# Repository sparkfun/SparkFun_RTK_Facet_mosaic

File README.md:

SparkPNT RTK Facet mosaic
========================================

[*SparkPNT RTK Facet mosaic (GPS-29688)*](https://www.sparkfun.com/sparkpnt-rtk-facet-mosaic.html)

Designed and manufactured in Boulder, Colorado, USA, and utilizing the multi-band mosaic-X5 from Septentrio, the [SparkPNT RTK Facet mosaic](https://www.sparkfun.com/sparkpnt-rtk-facet-mosaic.html) is *the* top of the line receiver for high precision geolocation and surveying needs. For basic users, it's incredibly easy to get up and running; for advanced users, the RTK Facet mosaic is a flexible and powerful tool. With just the press of a button, the RTK Facet mosaic is the fastest way to take centimeter-grade measurements. With a [subscription to the PointPerfect Flex NTRIP/RTCM service](https://www.sparkfun.com/rtk_facet_mosaic_registration) or any other corrections service, 10mm Real Time Kinematic fixes are less than a minute away. By connecting your phone to the RTK Facet mosaic over Bluetooth®, your phone or tablet can receive the NMEA output and work with most GIS software programs. This is exactly how $10,000 surveying devices have been operating for the past decade - we just made it faster, more precise, and a lot more economical.

The RTK Facet mosaic works with common GIS software for Android and iOS including SW Maps [Android](https://sparkfun.github.io/SparkFun_RTK_Firmware/gis_software/#sw-maps) / [iOS](https://apps.apple.com/us/app/sw-maps/id6444248083), [Field Genius](https://www.microsurvey.com/products/fieldgenius-for-android/), [SurvPC](https://www.carlsonsw.com/product/carlson-survce), [Survey Master](https://docs.sparkfun.com/SparkFun_RTK_Firmware/gis_software/#survey-master), [Vespucci](https://play.google.com/store/apps/details?id=de.blau.android&hl=en_US&gl=US), [QGIS](https://qgis.org/), [QField](https://docs.qfield.org/get-started/), and any GIS software that supports NMEA over Bluetooth.

Under the hood of the SparkPNT RTK Facet mosaic is an ESP32-WROVER-E connected to a mosaic-X5 GNSS multi-band receiver, and a variety of peripheral hardware (LiPo fuel gauge, microSD, etc). Additionally, housed under the dome of the RTK Facet mosaic is a surveyor grade L1/L2/L5 antenna. This antenna is a unique combination of elements designed to receive the GNSS signals (L1/L2/L5). The RTK Facet mosaic is programmed in Arduino and can be tailored by you to fit whatever your needs may be.

This device can be used in five modes:

- GNSS Positioning (~30cm accuracy) - also known as **Rover**
- GNSS Positioning with RTK (1.4cm accuracy) - also known as **Rover with RTK Fix**
- GNSS **Base Station**
- GNSS **Base Station NTRIP Server**

At *Power On* the device will enter **Rover** or **Base** mode; whichever state the device was in at the last power down. When the POWER/SETUP button is pressed momentarily, a menu is presented to change the RTK Facet mosaic from *Rover to Base mode* or vice-versa. The display will indicate the change with a small car *(Rover)* or flag *(Base)* icon.

In **Rover mode** the RTK Facet mosaic will receive `L1`, `L2`, and `L5` GNSS signals from the four constellations (GPS, GLONASS, Galileo, and BeiDou) and calculate the position based on these signals. Similar to a standard grade GPS receiver, the RTK Facet mosaic will output industry standard NMEA sentences at 4Hz and broadcast them over any paired Bluetooth® device. The end user will need to parse the NMEA sentences using commonly available mobile apps, GIS products, or embedded devices (there are many open source libraries). Unlike standard grade GPS receivers that have **2500mm** accuracy, the accuracy in this mode is approximately **300mm** horizontal positional accuracy. When RTCM correction data is sent over Bluetooth® or into the radio port, the device will automatically enter Positioning with RTK mode. In this mode RTK Facet mosaic will receive `L1`/`L2`/`L5` signals from the antenna and correction data from a base station. The receiver will quickly (within a second) obtain an RTK float, then fix. The NMEA sentences will have increased accuracy of 10mm horizontal and 10mm vertical accuracy. The RTCM correction data is most easily obtained over the Internet using a free app on your phone (see our SW Maps *([Android](http://docs.sparkfun.com/SparkFun_RTK_Everywhere_Firmware/gis_software_android/#sw-maps)/[iOS](http://docs.sparkfun.com/SparkFun_RTK_Everywhere_Firmware/gis_software_ios/#sw-maps))* or [Lefebure NTRIP](http://docs.sparkfun.com/SparkFun_RTK_Everywhere_Firmware/gis_software_android/#lefebure) instructions) and sent over Bluetooth® to the RTK Facet mosaic. However, RTCM correction data can also be received over an external cellular or radio link from a 2nd RTK Torch, Postcard, Facet mosaic, Surveyor, Express, etc. that is setup as a base station.

In **Base mode** the device will enter Base Station mode. This is used when the device is mounted to a fixed position (like a tripod or roof). The RTK Facet mosaic will initiate a survey. After 60 to 120 seconds the survey will complete and the RTK Facet mosaic will begin transmitting RTCM correction data out the radio port. A base is often used in conjunction with a second RTK Facet mosaic (or RTK Surveyor, Express, Express Plus, etc) unit set to *Rover* to obtain the 10mm accuracy. Said differently, the Base sits still and sends correction data to the Rover, so that the Rover can output really accurate position data for its location.

In addition to supplying position data, the RTK Facet mosaic is capable of logging NMEA, RAWX, and SFRBX for post processing making it ideal for research and advanced positioning applications.

The RTK Facet mosaic is an open source hardware product meaning you can fully obtain, see, and even modify the electrical and mechanical design files. This allows for easier maintenance and repair over time.

The SparkPNT RTK Facet mosaic kit includes everything you need: the enclosed device, thread adapter, charger, data cables, and carrying case. It does **NOT** include a [surveying pole](https://www.sparkfun.com/telescopic-surveying-pole.html) *(any additional items will need to be purchased separately)*.

> [!IMPORTANT]
> The SparkPNT RTK Facet mosaic is not designed for permanent outdoor mounting. Please use the [RTK mosaic-X5](https://www.sparkpnt.com/products/sparkpnt-sxm-e-cors) or the [RTK Reference Station](https://www.sparkfun.com/sparkfun-rtk-reference-station.html) that is located inside or protected from the elements. Or, for a DIY solution, the [ESP32](https://www.sparkfun.com/sparkfun-thing-plus-esp32-wroom-micro-b.html) attached to our [ZED-F9P breakout](https://www.sparkfun.com/sparkfun-gps-rtk-sma-breakout-zed-f9p-qwiic.html) is a great way to go. See our [How to Build a DIY GNSS Reference Station](https://learn.sparkfun.com/tutorials/how-to-build-a-diy-gnss-reference-station) tutorial for more information.

> [!NOTE]
> The [RTK Everywhere firmware](https://github.com/sparkfun/SparkFun_RTK_Everywhere_Firmware) is open-source, so users can obtain, check, and even modify the device's functionality. This allows for easier feature expansion, bug maintenance, and longer device longevity.

Documentation
--------------

- **[Hookup Guide (mkdocs)](http://docs.sparkfun.com/SparkFun_RTK_Facet_mosaic/)** - The hookup guide for the SparkPNT RTK Facet mosaic hosted by GitHub pages.<br>
   
- [User Manual - RTK Everywhere Firmware](https://docs.sparkfun.com/SparkFun_RTK_Everywhere_Firmware/) - Documentation for the [RTK Everywhere firmware](https://github.com/sparkfun/SparkFun_RTK_Everywhere_Firmware)

*Need to download or print our hookup guide?*

- [Print *(Print to PDF)* from Single-Page View](http://docs.sparkfun.com/SparkFun_RTK_Facet_mosaic/print_view)

Repository Contents
-------------------

- **[/docs](/docs/)** - Online documentation files
	- [assets](/docs/assets/) - Assets files
		- [3d_model](/docs/assets/3d_model/) - Files for the 3D models
			- [3D CAD Models](/docs/assets/3d_model/step_files.zip) (.step)
		- [board_files](/docs/assets/board_files/) - Files for the product design
			- [KiCad Design Files](/docs/assets/board_files/kicad_files.zip) (.zip)
			- [Schematics](/docs/assets/board_files/schematics.zip) (.pdf)
			<!-- - [Dimensions](/docs/assets/board_files/dimensions.pdf) (.pdf) -->
		- [component_documentation](/docs/assets/component_documentation/) - Datasheets for hardware components
		- [img/hookup_guide/](/docs/assets/img/hookup_guide/) - Images for hookup guide documentation
- **[/Enclosure](/Enclosure/)** - CAD model for an enclosure
- **[/Hardware](/Hardware/)** - Hardware design files (.brd, .sch)
	- **[/Production](/Production/)** - Production files

Product Variants
----------------

- [GPS-24903](https://www.sparkfun.com/sparkpnt-rtk-facet-mosaic-l-band.html) - v1.0, Initial Release
- [GPS-29688](https://www.sparkfun.com/sparkpnt-rtk-facet-mosaic.html) - Rename the product to remove "L-Band" from the name. This is due to u-blox's choice to discontinue the L-Band service to North America starting on December 31st, 2025.

- Facet Product Line
	- [GPS-20000](https://www.sparkfun.com/sparkfun-rtk-facet-l-band.html) - SparkFun RTK Facet L-Band
	- [GPS-19984](https://www.sparkfun.com/sparkfun-rtk-facet.html) - SparkFun RTK Facet
	- [GPS-19029](https://www.sparkfun.com/sparkfun-rtk-facet.html) - SparkFun RTK Facet *(Initial Release)*
- mosaic-`XX` GNSS Module
	- [SXT](https://www.sparkpnt.com/products/sxt-gnssdo) - SparkPNT GNSS Disciplined Oscillator
	- [SXM-E](https://www.sparkpnt.com/products/sparkpnt-sxm-e-cors) - SparkFun RTK mosaic-X5
	- [GPS-23088](https://www.sparkfun.com/sparkfun-triband-gnss-rtk-breakout-mosaic-x5.html) - SparkFun Triband GNSS RTK Breakout - mosaic-X5

License Information
-------------------

This product is ***open source***!

Please review the [`LICENSE.md`](./LICENSE.md) file for license information.

If you have any questions or concerns about licensing, please contact technical support on our [SparkFun forums](https://community.sparkfun.com/).

Distributed as-is; no warranty is given.

- Your friends at SparkPNT.

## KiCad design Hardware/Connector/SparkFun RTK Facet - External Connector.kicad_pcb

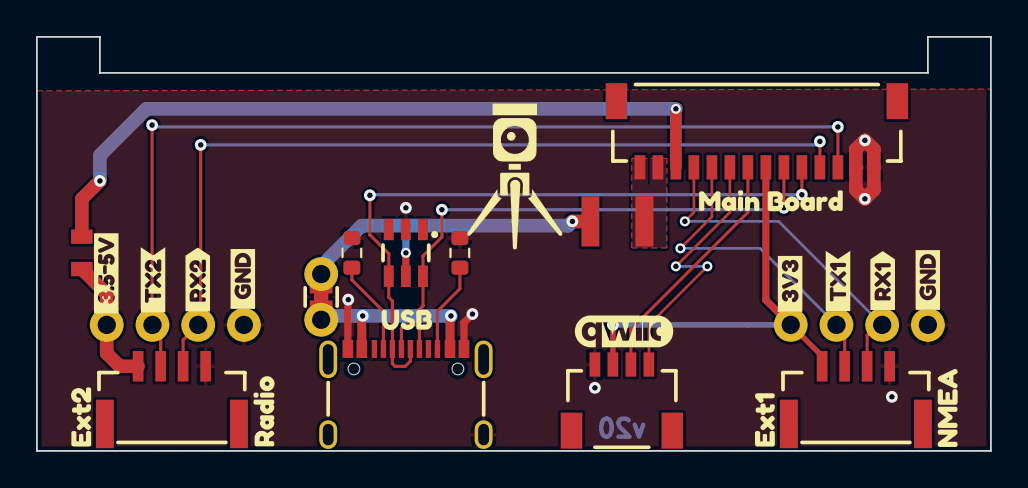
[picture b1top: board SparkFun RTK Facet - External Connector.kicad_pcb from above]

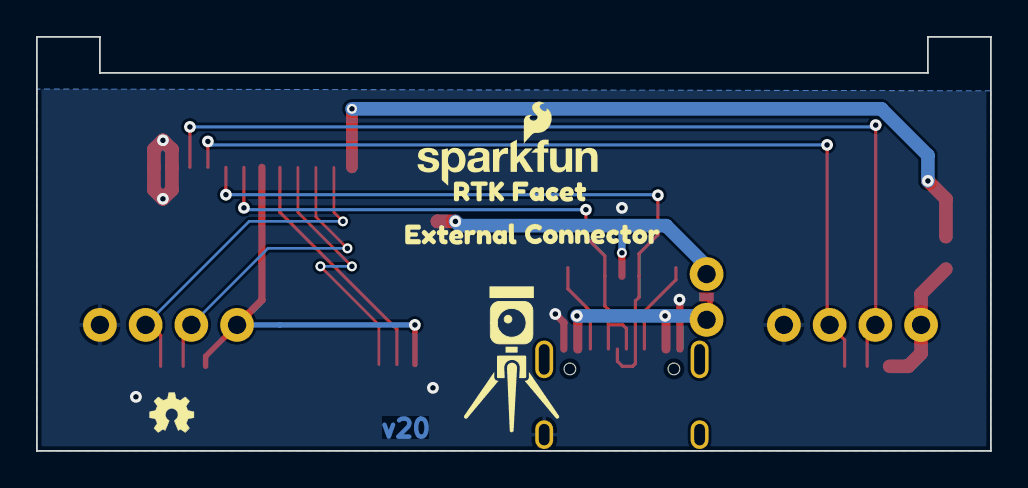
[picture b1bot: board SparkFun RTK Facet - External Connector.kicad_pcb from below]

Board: 2 copper layers, 53.0 x 23.0 mm, 35 parts (6 on the bottom side), 17 nets.

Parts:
D1: DT1042-04SO; SOT23-6
F1: 6V/0.5A/1A; 0805
F3: 6V/2.0A/4.0A; 1210
G3: OSHW_Logo; Creative_Commons_License
J1: Conn_01x14; JST_SMD_1.0mm-14_RA
J2, J9: JST_Locking_4; JST_SMD_1.25mm-4_Locking
J4: Qwiic_RA; JST_SMD_1.0mm-4_RA
J5: USB_C_Receptacle; USB-C_16
J11, J12: Conn_01x04; 1x04
JP0: Measure; Jumper_2_PTH_SMD_Combo-NC
LOGO1: OSHW-LOGOMINI; OSHW_Logo_2.5mm
LOGO2: SFE_LOGO_NAME_FLAME.1_INCH; SparkFun_Logo_10mm
R16, R17: 5.1k; R_0603_1608Metric
Ref**: Val**; SparkFun_RTK_20mm
Ref**#2: Val**; SparkFun_RTK_20mm
kibuzzard-66F4BFD6: G***; kibuzzard-66F4BFD6
kibuzzard-66F4BFE6: G***; kibuzzard-66F4BFE6
kibuzzard-66F4BFEC: G***; kibuzzard-66F4BFEC
kibuzzard-66F4C0A3: G***; kibuzzard-66F4C0A3
kibuzzard-66F4C0CF: G***; kibuzzard-66F4C0CF
kibuzzard-66F4C0D4: G***; kibuzzard-66F4C0D4
kibuzzard-66F4C0DF: G***; kibuzzard-66F4C0DF
kibuzzard-66F4C0F8: G***; kibuzzard-66F4C0F8
kibuzzard-66F4C0FC: G***; kibuzzard-66F4C0FC
kibuzzard-66F4C1AD: G***; kibuzzard-66F4C1AD
kibuzzard-66F4C03C, kibuzzard-66F4C03C#2: G***; kibuzzard-66F4C03C
kibuzzard-66F4C09A: G***; kibuzzard-66F4C09A
kibuzzard-66F4C18F: G***; kibuzzard-66F4C18F
kibuzzard-66F4C088: G***; kibuzzard-66F4C088
kibuzzard-66F4C199: G***; kibuzzard-66F4C199
kibuzzard-66FF0C1C: G***; kibuzzard-66FF0C1C

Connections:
3.3V: J1.7, J2.1, J4.2, J12.4
ESP21/SDA: J1.8, J4.3
ESP22/SCL: J1.9, J4.4
ExternalDATA_RXI: J1.11, J2.3, J12.2
ExternalDATA_TXO: J1.10, J2.2, J12.3
GND: D1.2 (GND), J1.1, J1.2, J2.4, J4.1, J5.GND, J5.S (SHIELD), J9.4, J11.1, J12.1, R16.2, R17.2
unnamed: D1.5 (VCC), F3.2, JP0.2 (B)
unnamed: J5.A5 (CC1), R17.1
unnamed: J5.B5 (CC2), R16.1
unnamed: F1.2, J9.1, J11.4
unnamed: J5.VBUS, JP0.1 (A)
USB_DM: D1.4 (I/O3), J1.5, J5.A7 (D-), J5.B7 (D-)
USB_DP: D1.6 (I/O4), J1.6, J5.A6 (D+), J5.B6 (D+)
VBATT: F1.1, J1.12
VUSB: F3.1, J1.13, J1.14
ZED_RXI2: J1.4, J9.3, J11.2
ZED_TXO2: J1.3, J9.2, J11.3

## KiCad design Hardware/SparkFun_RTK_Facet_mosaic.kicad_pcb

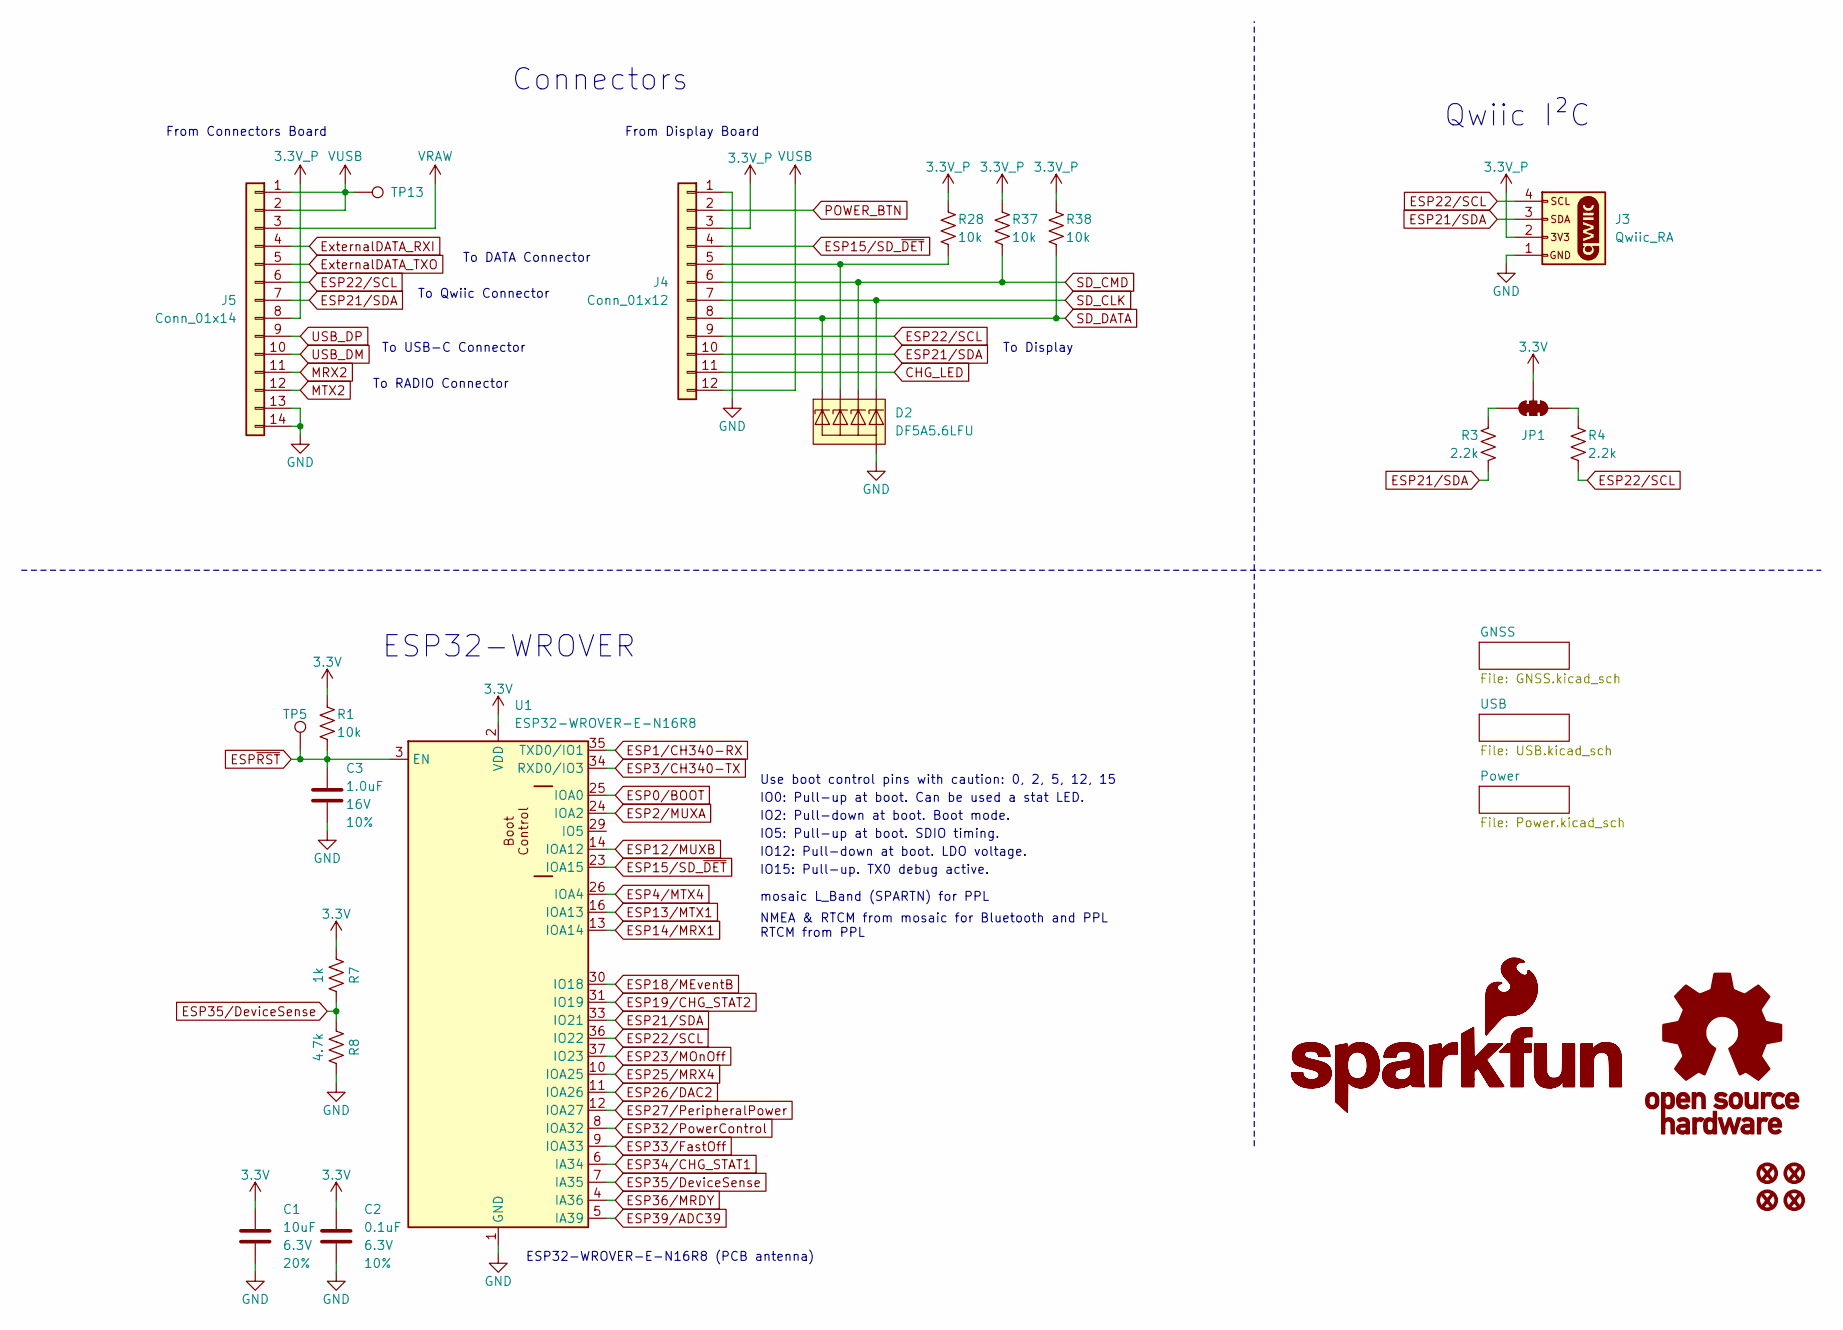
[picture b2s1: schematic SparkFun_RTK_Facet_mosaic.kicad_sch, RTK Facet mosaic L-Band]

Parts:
C1: 10uF; C_0402_1005Metric; Voltage 6.3V; Tolerance 20%
C2: 0.1uF; C_0402_1005Metric; Voltage 6.3V; Tolerance 10%
C3: 1.0uF; C_0402_1005Metric; Voltage 16V; Tolerance 10%
D2: DF5A5.6LFU; SOT-353
FID1, FID2, FID3, FID4: Fiducial_0.5mm; Fiducial_0.5mm_Mask1mm
G1: OSHW_Logo; Creative_Commons_License
G3: SparkFun_Logo
G5: SparkFun_Logo; SparkFun_Logo_8mm
J3: Qwiic_RA; JST_SMD_1.0mm-4_RA
J4: Conn_01x12; JST_SMD_1.0mm-12_RA
J5: Conn_01x14; JST_SMD_1.0mm-14_RA
JP1: Jumper_3_NC-2_Trace
R1, R28, R37, R38: 10k; R_0402_1005Metric
R3, R4: 2.2k; R_0402_1005Metric
R7: 1k; R_0402_1005Metric
R8: 4.7k; R_0402_1005Metric
TP5, TP13: PTH; 1x01
U1: ESP32-WROVER-E-N16R8; ESP32-WROVER-E-IE

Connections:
3.3V: C1.1, C2.1, JP1.2 (C), R1.1, R7.1, U1.2 (VDD); also elsewhere on the board
3.3V_P: J3.2, J4.3, J5.8, R28.1, R37.1, R38.1; also elsewhere on the board
CHG_LED: J4.11; also elsewhere on the board
ESP0/BOOT: U1.25 (IOA0); also elsewhere on the board
ESP1/CH340-RX: U1.35 (TXD0/IO1); also elsewhere on the board
ESP2/MUXA: U1.24 (IOA2); also elsewhere on the board
ESP3/CH340-TX: U1.34 (RXD0/IO3); also elsewhere on the board
ESP4/MTX4: U1.26 (IOA4); also elsewhere on the board
ESP12/MUXB: U1.14 (IOA12); also elsewhere on the board
ESP13/MTX1: U1.16 (IOA13); also elsewhere on the board
ESP14/MRX1: U1.13 (IOA14); also elsewhere on the board
ESP15/SD_~DET: J4.4, U1.23 (IOA15)
ESP18/MEventB: U1.30 (IO18); also elsewhere on the board
ESP19/CHG_STAT2: U1.31 (IO19); also elsewhere on the board
ESP23/MOnOff: U1.37 (IO23); also elsewhere on the board
ESP25/MRX4: U1.10 (IOA25); also elsewhere on the board
ESP26/DAC2: U1.11 (IOA26); also elsewhere on the board
ESP27/PeripheralPower: U1.12 (IOA27); also elsewhere on the board
ESP32/PowerControl: U1.8 (IOA32); also elsewhere on the board
ESP33/FastOff: U1.9 (IOA33); also elsewhere on the board
ESP34/CHG_STAT1: U1.6 (IA34); also elsewhere on the board
ESP35/DeviceSense: R7.2, R8.1, U1.7 (IA35)
ESP36/MRDY: U1.4 (IA36); also elsewhere on the board
ESP39/ADC39: U1.5 (IA39); also elsewhere on the board
ExternalDATA_RXI: J5.4; also elsewhere on the board
ExternalDATA_TXO: J5.5; also elsewhere on the board
GND: C1.2, C2.2, C3.2, D2.2 (A), J3.1, J4.1, J5.13, J5.14, R8.2, U1.1 (GND), U1.15 (GND), U1.38 (GND), U1.39.1 (GND), U1.39.2 (GND), U1.39.3 (GND), U1.39.4 (GND), U1.39.5 (GND), U1.39.6 (GND), U1.39.7 (GND), U1.39.8 (GND), U1.39.9 (GND); also elsewhere on the board
MRX2: J5.11; also elsewhere on the board
MTX2: J5.12; also elsewhere on the board
unnamed: D2.3 (K2), J4.5, R28.2
POWER_BTN: J4.2; also elsewhere on the board
SD_CLK: D2.5 (K4), J4.7; also elsewhere on the board
SD_CMD: D2.4 (K3), J4.6, R37.2; also elsewhere on the board
SD_DATA: D2.1 (K1), J4.8, R38.2; also elsewhere on the board
USB_DM: J5.10; also elsewhere on the board
USB_DP: J5.9; also elsewhere on the board
VRAW: J5.3; also elsewhere on the board
VUSB: J4.12, J5.1, J5.2, TP13.1; also elsewhere on the board

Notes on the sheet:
IO15: Pull-up. TX0 debug active.
IO2: Pull-down at boot. Boot mode.
To Display
To DATA Connector
To Qwiic Connector
ESP32-WROVER
IO0: Pull-up at boot. Can be used a stat LED.
mosaic L_Band (SPARTN) for PPL
Qwiic I²C
To RADIO Connector
From Connectors Board
IO5: Pull-up at boot. SDIO timing.
To USB-C Connector
From Display Board
Connectors
Use boot control pins with caution: 0, 2, 5, 12, 15
ESP32-WROVER-E-N16R8 (PCB antenna)
NMEA & RTCM from mosaic for Bluetooth and PPL RTCM from PPL
IO12: Pull-down at boot. LDO voltage.

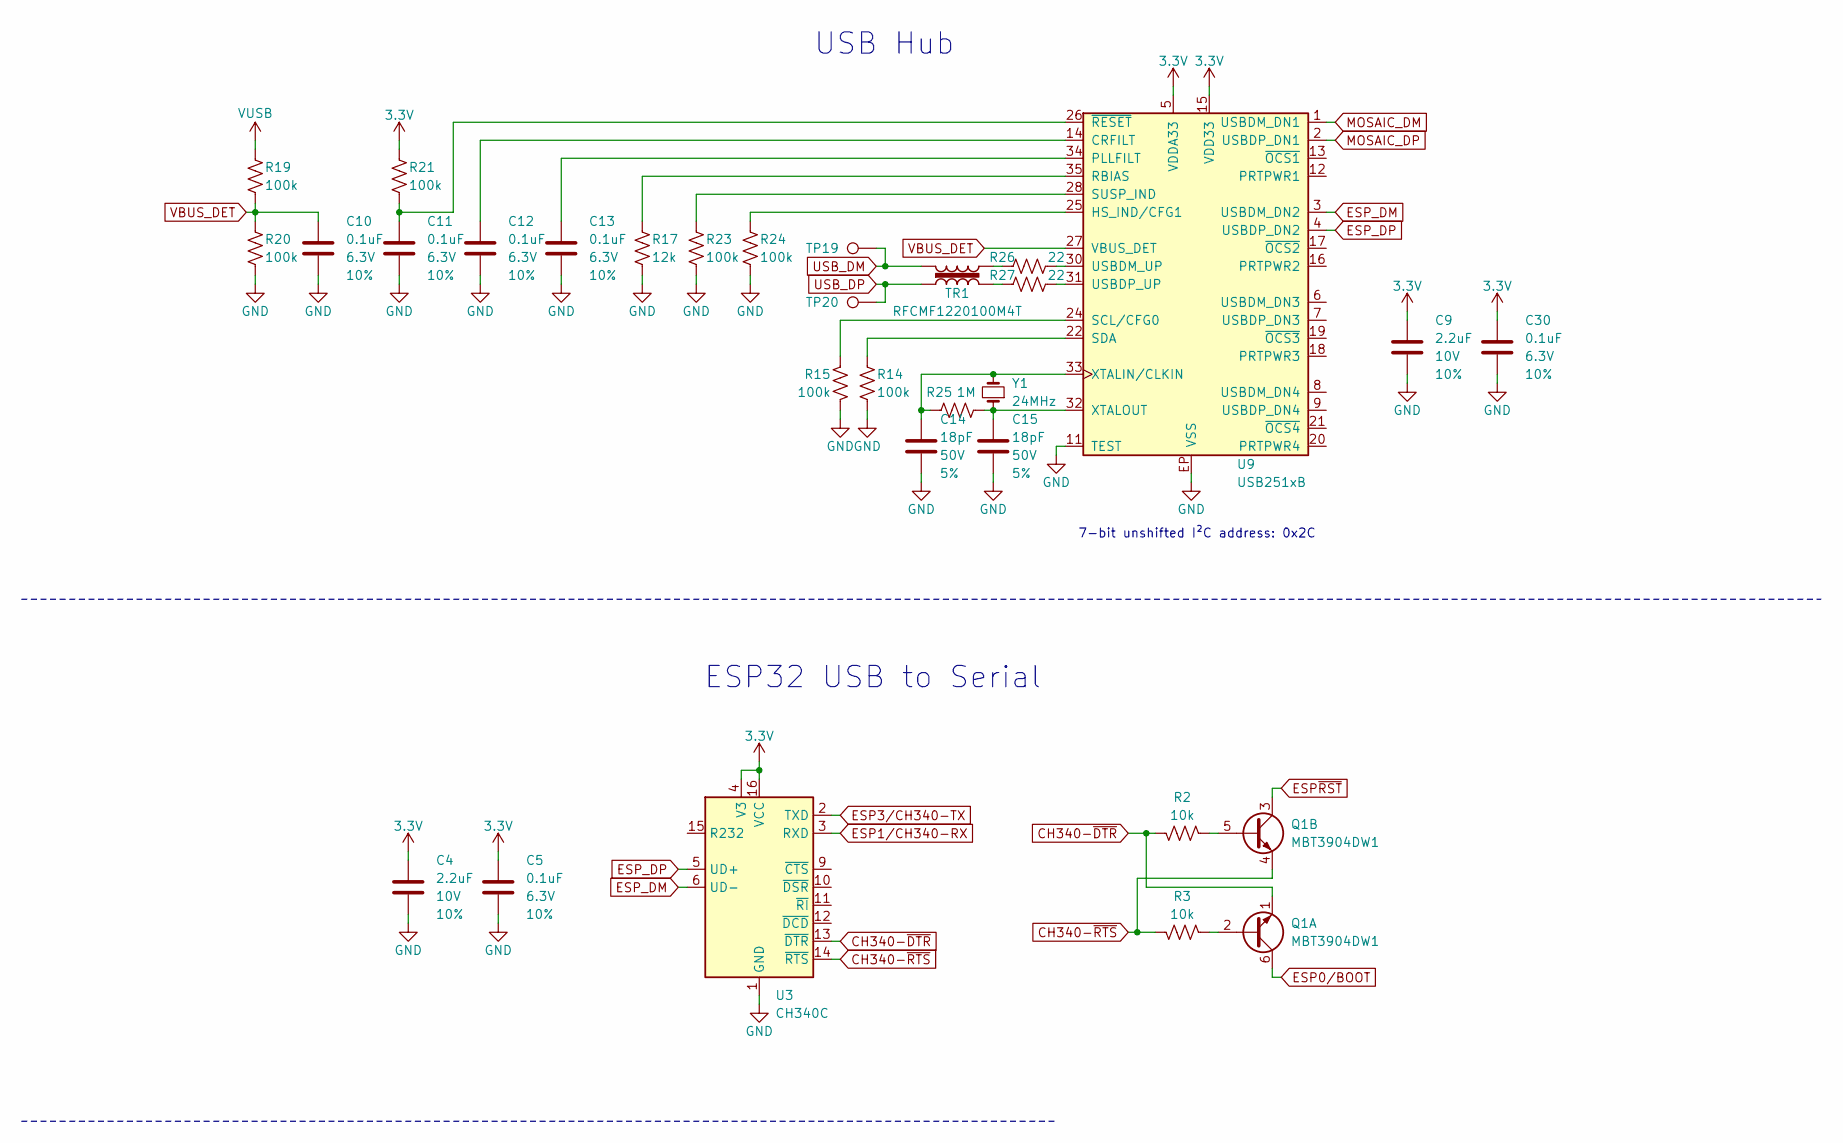
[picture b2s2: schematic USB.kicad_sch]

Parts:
C4, C9: 2.2uF; C_0402_1005Metric; Voltage 10V; Tolerance 10%
C5, C10, C11, C12, C13, C30: 0.1uF; C_0402_1005Metric; Voltage 6.3V; Tolerance 10%
C14, C15: 18pF; C_0603_1608Metric; Voltage 50V; Tolerance 5%
Q1: MBT3904DW1; SOT-323
R2, R3: 10k; R_0402_1005Metric
R14, R15, R19, R20, R21, R23, R24: 100k; R_0402_1005Metric
R17: 12k; R_0402_1005Metric
R25: 1M; R_0402_1005Metric
R26, R27: 22; R_0402_1005Metric
TP19, TP20: 1.0mm; TestPoint-1.0mm
TR1: RFCMF1220100M4T
U3: CH340C; SO-16
U9: USB251xB; QFN-36
Y1: 24MHz; Crystal_SMD_2.0x1.6mm

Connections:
3.3V: C4.1, C5.1, C9.1, C30.1, R21.1, U3.4 (V3), U3.16 (VCC), U9.5 (VDDA33), U9.10 (VDDA33), U9.15 (VDD33), U9.23 (VDD33), U9.29 (VDDA33), U9.36 (VDDA33); also elsewhere on the board
CH340-~DTR: Q1.1 (E1), R2.2, U3.13 (~DTR)
ESP0/BOOT: Q1.6 (C1); also elsewhere on the board
ESP1/CH340-RX: U3.3 (RXD); also elsewhere on the board
ESP3/CH340-TX: U3.2 (TXD); also elsewhere on the board
ESP_DM: U3.6 (UD-), U9.3 (USBDM_DN2)
ESP_DP: U3.5 (UD+), U9.4 (USBDP_DN2)
GND: C4.2, C5.2, C9.2, C10.2, C11.2, C12.2, C13.2, C14.2, C15.2, C30.2, R14.2, R15.2, R17.1, R20.2, R23.2, R24.2, U3.1 (GND), U9.11 (TEST), U9.EP (VSS); also elsewhere on the board
MOSAIC_DM: U9.1 (USBDM_DN1); also elsewhere on the board
MOSAIC_DP: U9.2 (USBDP_DN1); also elsewhere on the board
unnamed: Q1.5 (B2), R2.1
unnamed: R26.2, TR1.2
unnamed: R27.2, TR1.4
unnamed: C12.1, U9.14 (CRFILT)
unnamed: R24.1, U9.25 (HS_IND/CFG1)
unnamed: C13.1, U9.34 (PLLFILT)
unnamed: R17.2, U9.35 (RBIAS)
unnamed: R15.1, U9.24 (SCL/CFG0)
unnamed: R14.1, U9.22 (SDA)
unnamed: R23.1, U9.28 (SUSP_IND)
unnamed: R26.1, U9.30 (USBDM_UP)
unnamed: R27.1, U9.31 (USBDP_UP)
unnamed: C14.1, R25.2, U9.33 (XTALIN/CLKIN), Y1.2
unnamed: C15.1, R25.1, U9.32 (XTALOUT), Y1.1
unnamed: C11.1, R21.2, U9.26 (~RESET)
USB_DM: TP19.1, TR1.1; also elsewhere on the board
USB_DP: TP20.1, TR1.3; also elsewhere on the board
VBUS_DET: C10.1, R19.2, R20.1, U9.27 (VBUS_DET)
VUSB: R19.1; also elsewhere on the board

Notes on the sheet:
ESP32 USB to Serial
7-bit unshifted I²C address: 0x2C
USB Hub

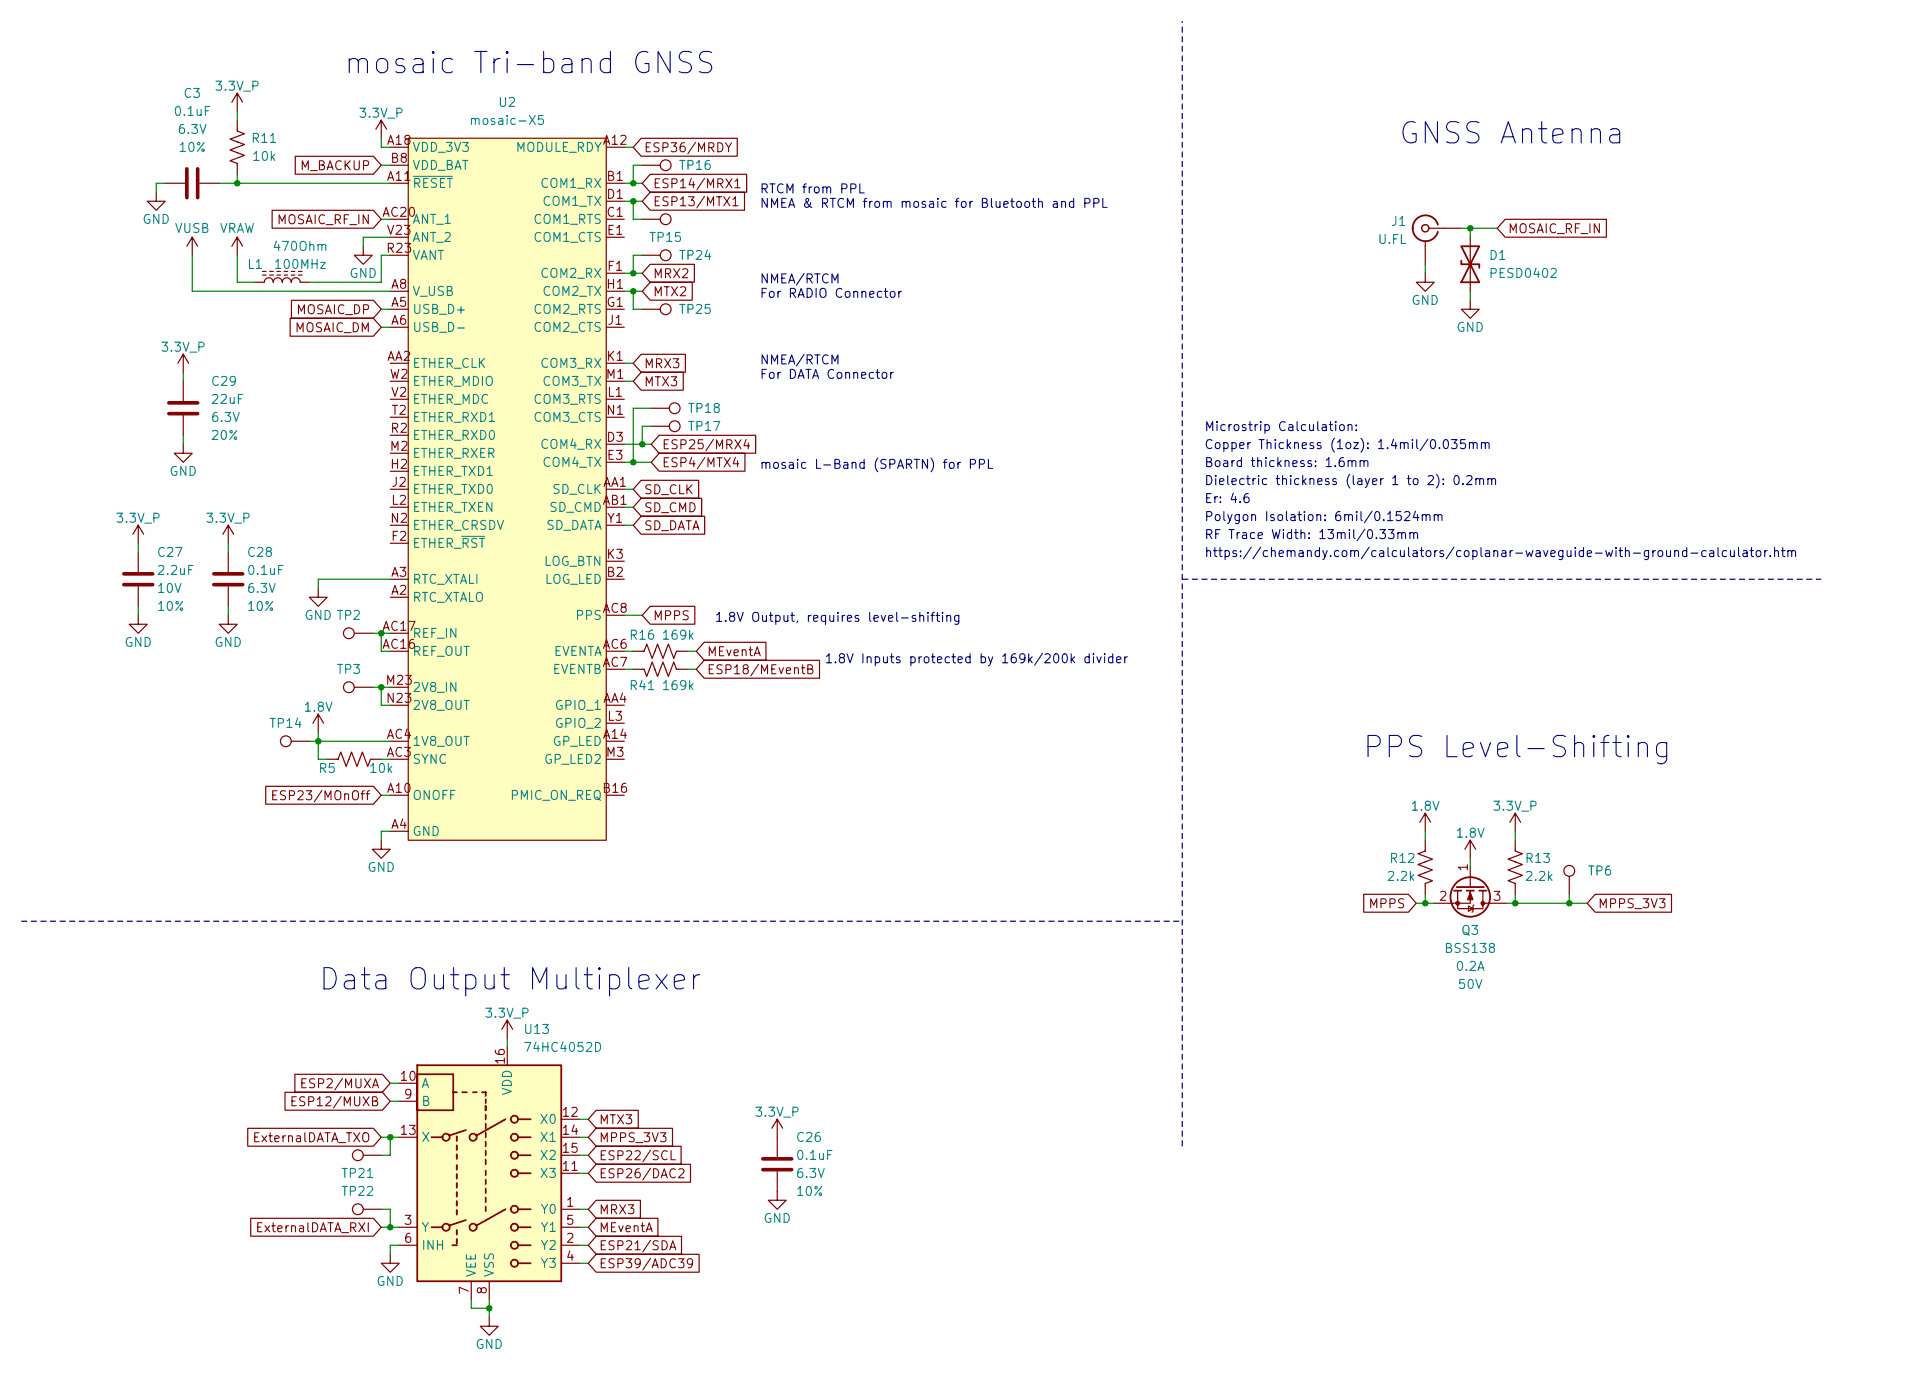
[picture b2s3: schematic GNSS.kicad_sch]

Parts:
C3, C26, C28: 0.1uF; C_0402_1005Metric; Voltage 6.3V; Tolerance 10%
C27: 2.2uF; C_0402_1005Metric; Voltage 10V; Tolerance 10%
C29: 22uF; C_0603_1608Metric; Voltage 6.3V; Tolerance 20%
D1: PESD0402; C_0402_1005Metric
J1: U.FL
L1: 470Ohm; C_0603_1608Metric
Q3: BSS138; SOT23-3
R5, R11: 10k; R_0402_1005Metric
R12, R13: 2.2k; R_0402_1005Metric
R16, R41: 169k; R_0603_1608Metric
TP2, TP3, TP14, TP15, TP16, TP17, TP18, TP24, TP25: 1.0mm; TestPoint-1.0mm
TP6, TP21, TP22: PTH; 1x01
U2: mosaic-X5; MOSAIC_LGA
U13: 74HC4052D; SO-16

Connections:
1.8V: Q3.1 (G), R5.2, R12.1, TP14.1, U2.AC4 (1V8_OUT)
3.3V_P: C26.1, C27.1, C28.1, C29.1, R11.1, R13.1, U2.A18 (VDD_3V3), U2.A19 (VDD_3V3), U2.A20 (VDD_3V3), U2.B18 (VDD_3V3), U2.B19 (VDD_3V3), U2.B20 (VDD_3V3), U2.C18 (VDD_3V3), U2.C19 (VDD_3V3), U2.C20 (VDD_3V3), U13.16 (VDD); also elsewhere on the board
ESP2/MUXA: U13.10 (A); also elsewhere on the board
ESP4/MTX4: TP18.1, U2.E3 (COM4_TX); also elsewhere on the board
ESP12/MUXB: U13.9 (B); also elsewhere on the board
ESP13/MTX1: TP15.1, U2.D1 (COM1_TX); also elsewhere on the board
ESP14/MRX1: TP16.1, U2.B1 (COM1_RX); also elsewhere on the board
ESP18/MEventB: R41.1; also elsewhere on the board
ESP23/MOnOff: U2.A10 (ONOFF); also elsewhere on the board
ESP25/MRX4: TP17.1, U2.D3 (COM4_RX); also elsewhere on the board
ESP26/DAC2: U13.11 (X3); also elsewhere on the board
ESP36/MRDY: U2.A12 (MODULE_RDY); also elsewhere on the board
ESP39/ADC39: U13.4 (Y3); also elsewhere on the board
ExternalDATA_RXI: TP22.1, U13.3 (Y); also elsewhere on the board
ExternalDATA_TXO: TP21.1, U13.13 (X); also elsewhere on the board
GND: C3.2, C26.2, C27.2, C28.2, C29.2, D1.1 (A1), J1.2 (Ext), U2.A3 (RTC_XTALI), U2.A4 (GND), U2.A7 (GND), U2.A15 (GND), U2.A16 (GND), U2.A17 (GND), U2.A21 (GND), U2.A22 (GND), U2.A23 (GND), U2.AA13 (GND), U2.AA14 (GND), U2.AA15 (GND), U2.AA16 (GND), U2.AA17 (GND), U2.AA18 (GND), U2.AA19 (GND), U2.AA20 (GND), U2.AA21 (GND), U2.AA22 (GND), U2.AA23 (GND), U2.AB2 (GND), U2.AB3 (GND), U2.AB4 (GND), U2.AB5 (GND), U2.AB6 (GND), U2.AB7 (GND), U2.AB8 (GND), U2.AB13 (GND), U2.AB14 (GND), U2.AB15 (GND), U2.AB16 (GND), U2.AB17 (GND), U2.AB18 (GND), U2.AB19 (GND), U2.AB20 (GND), U2.AB21 (GND), U2.AB22 (GND), U2.AB23 (GND), U2.AC13 (GND), U2.AC15 (GND), U2.AC18 (GND), U2.AC19 (GND), U2.AC21 (GND), U2.AC22 (GND), U2.AC23 (GND), U2.B4 (GND), U2.B5 (GND), U2.B6 (GND), U2.B7 (GND), U2.B13 (GND), U2.B17 (GND), U2.B21 (GND), U2.C4 (GND), U2.C7 (GND), U2.C15 (GND), U2.C16 (GND), U2.C17 (GND), U2.C23 (GND), U2.D2 (GND), U2.D21 (GND), U2.D22 (GND), U2.D23 (GND), U2.E2 (GND), U2.E21 (GND), U2.E22 (GND), U2.E23 (GND), U2.F21 (GND), U2.F22 (GND), U2.F23 (GND), U2.G2 (GND), U2.G21 (GND), U2.G23 (GND), U2.H21 (GND), U2.H22 (GND), U2.H23 (GND), U2.J21 (GND), U2.J22 (GND), U2.J23 (GND), U2.K2 (GND), U2.K21 (GND), U2.K22 (GND), U2.K23 (GND), U2.L21 (GND), U2.L22 (GND), U2.L23 (GND), U2.M21 (GND), U2.M22 (GND), U2.N21 (GND), U2.N22 (GND), U2.P1 (GND), U2.P2 (GND), U2.P3 (GND), U2.P21 (GND), U2.P22 (GND), U2.R3 (GND), U2.R21 (GND), U2.R22 (GND), U2.T21 (GND), U2.T22 (GND), U2.T23 (GND), U2.U2 (GND), U2.U21 (GND), U2.U22 (GND), U2.U23 (GND), U2.V21 (GND), U2.V22 (GND), U2.V23 (ANT_2), U2.W21 (GND), U2.W22 (GND), U2.W23 (GND), U2.Y2 (GND), U2.Y21 (GND), U2.Y22 (GND), U2.Y23 (GND), U13.6 (INH), U13.7 (VEE), U13.8 (VSS); also elsewhere on the board
MEventA: R16.1, U13.5 (Y1)
MOSAIC_DM: U2.A6 (USB_D-); also elsewhere on the board
MOSAIC_DP: U2.A5 (USB_D+); also elsewhere on the board
MOSAIC_RF_IN: D1.2 (A2), J1.1 (In), U2.AC20 (ANT_1)
MPPS: Q3.2 (S), R12.2, U2.AC8 (PPS)
MPPS_3V3: Q3.3 (D), R13.2, TP6.1, U13.14 (X1)
MRX2: TP24.1, U2.F1 (COM2_RX); also elsewhere on the board
MRX3: U2.K1 (COM3_RX), U13.1 (Y0)
MTX2: TP25.1, U2.H1 (COM2_TX); also elsewhere on the board
MTX3: U2.M1 (COM3_TX), U13.12 (X0)
M_BACKUP: U2.B8 (VDD_BAT); also elsewhere on the board
unnamed: TP3.1, U2.M23 (2V8_IN), U2.N23 (2V8_OUT)
unnamed: R16.2, U2.AC6 (EVENTA)
unnamed: R41.2, U2.AC7 (EVENTB)
unnamed: TP2.1, U2.AC16 (REF_OUT), U2.AC17 (REF_IN)
unnamed: R5.1, U2.AC3 (SYNC)
SD_CLK: U2.AA1 (SD_CLK); also elsewhere on the board
SD_CMD: U2.AB1 (SD_CMD); also elsewhere on the board
SD_DATA: U2.Y1 (SD_DATA); also elsewhere on the board
VANT: L1.2, U2.P23 (VANT), U2.R23 (VANT)
VRAW: L1.1; also elsewhere on the board
VUSB: U2.A8 (V_USB); also elsewhere on the board

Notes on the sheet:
Er: 4.6
mosaic L-Band (SPARTN) for PPL
Polygon Isolation: 6mil/0.1524mm
Dielectric thickness (layer 1 to 2): 0.2mm
RTCM from PPL NMEA & RTCM from mosaic for Bluetooth and PPL
Board thickness: 1.6mm
mosaic Tri-band GNSS
Microstrip Calculation:
NMEA/RTCM For RADIO Connector
Data Output Multiplexer
NMEA/RTCM For DATA Connector
https://chemandy.com/calculators/coplanar-waveguide-with-ground-calculator.htm
Copper Thickness (1oz): 1.4mil/0.035mm
PPS Level-Shifting
1.8V Output, requires level-shifting
1.8V Inputs protected by 169k/200k divider
GNSS Antenna
RF Trace Width: 13mil/0.33mm

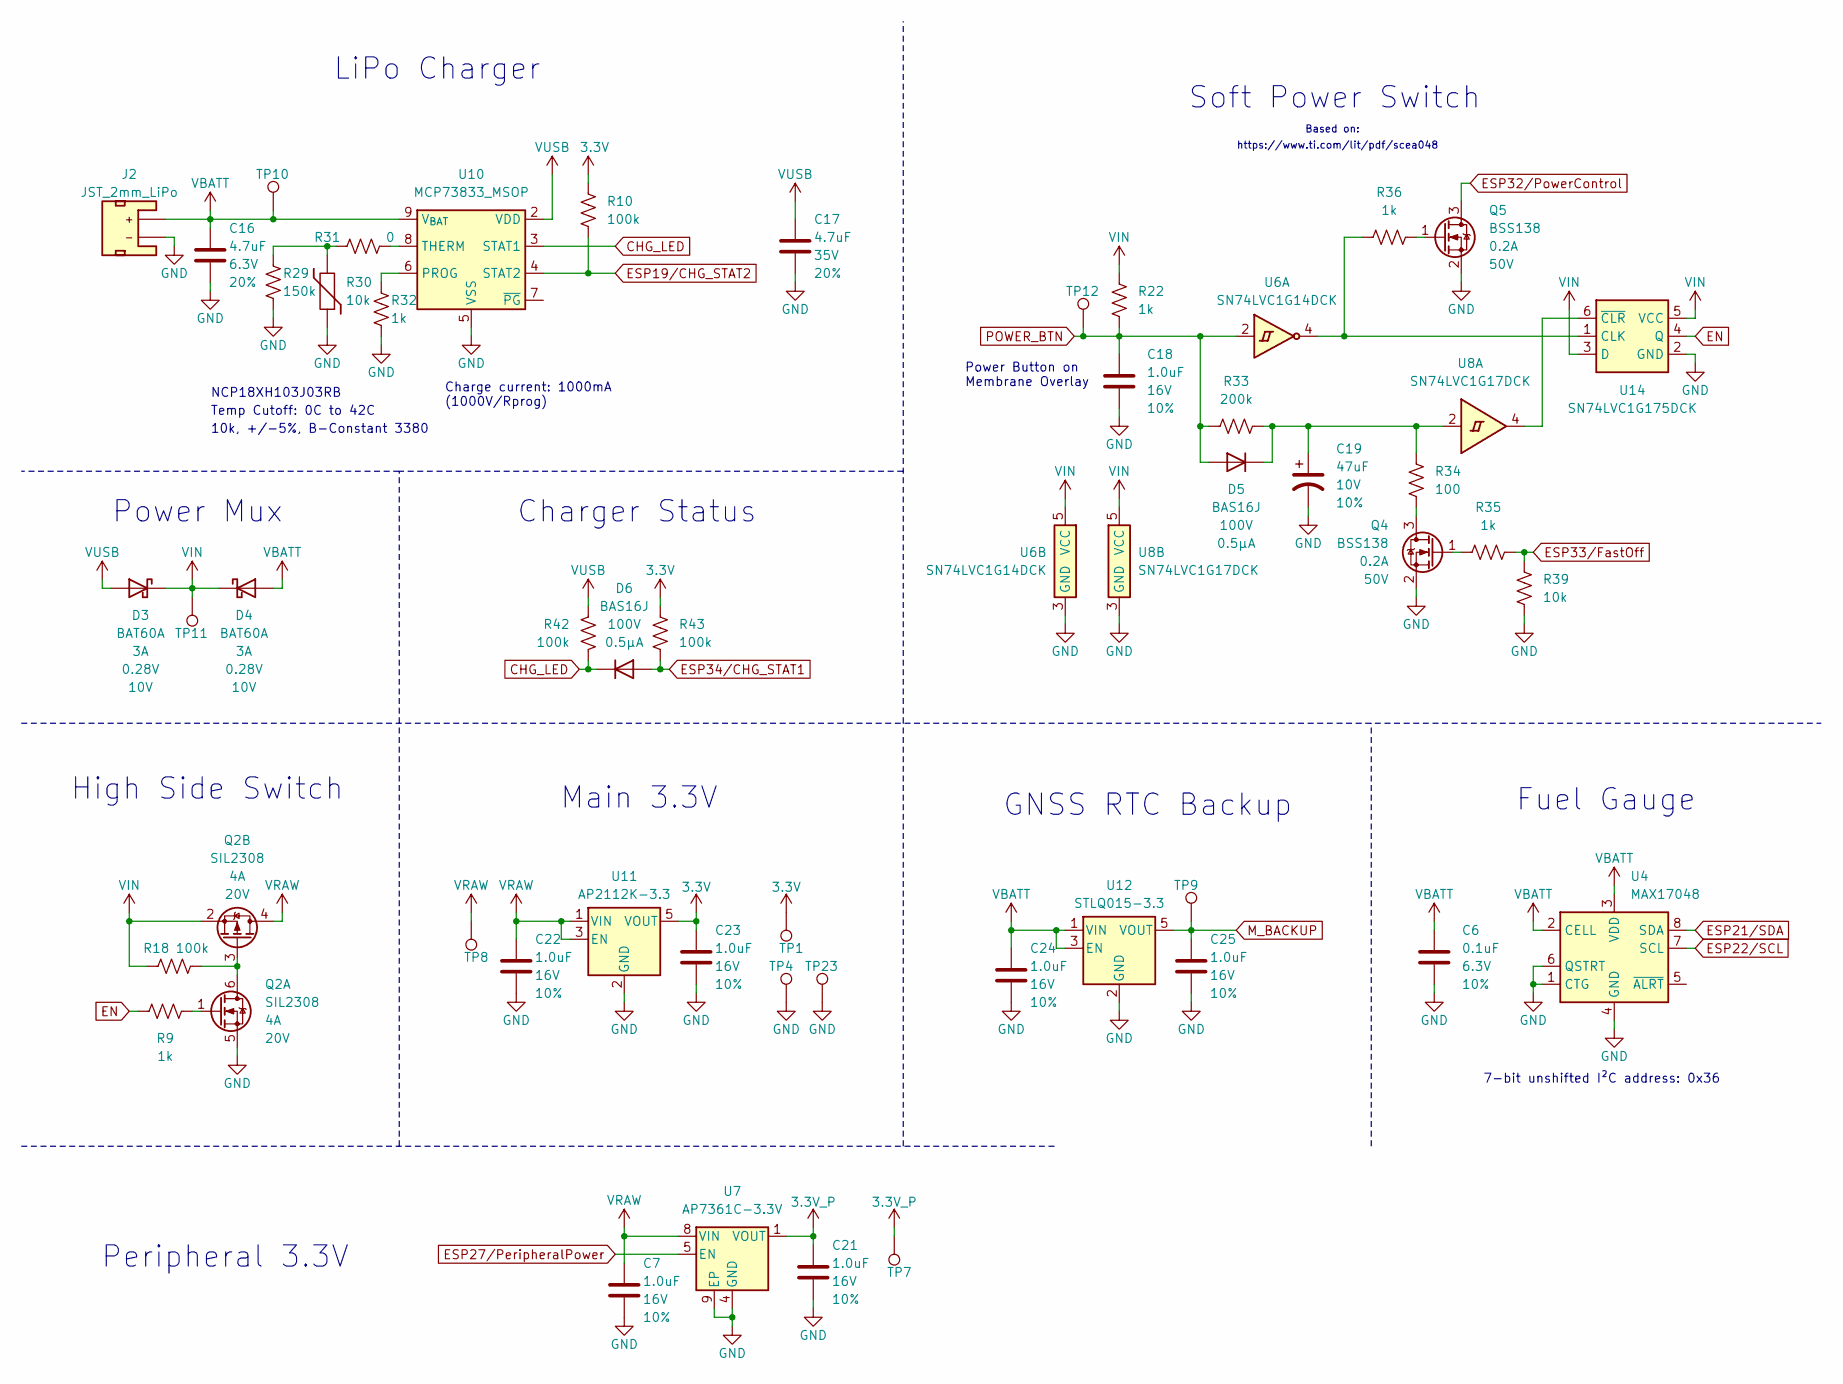
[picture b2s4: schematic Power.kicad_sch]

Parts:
C6: 0.1uF; C_0402_1005Metric; Voltage 6.3V; Tolerance 10%
C7, C18, C21, C22, C23, C24, C25: 1.0uF; C_0402_1005Metric; Voltage 16V; Tolerance 10%
C16: 4.7uF; C_0402_1005Metric; Voltage 6.3V; Tolerance 20%
C17: 4.7uF; C_0603_1608Metric; Voltage 35V; Tolerance 20%
C19: 47uF; EIA-3528; Voltage 10V; Tolerance 10%
D3, D4: BAT60A; SOD-323
D5, D6: BAS16J; SOD-323
J2: JST_2mm_LiPo; JST_SMD_2.0mm-2
Q2: SIL2308; SOT23-6-Tight
Q4, Q5: BSS138; SOT23-3
R9, R22, R32, R35, R36: 1k; R_0402_1005Metric
R10, R18, R42, R43: 100k; R_0402_1005Metric
R29: 150k; R_0402_1005Metric
R30: 10k; R_0603_1608Metric
R31: 0; R_0402_1005Metric
R33: 200k; R_0402_1005Metric
R34: 100; R_0603_1608Metric
R39: 10k; R_0402_1005Metric
TP1, TP4, TP7, TP8, TP9, TP10, TP11, TP12, TP23: PTH; 1x01
U4: MAX17048; DFN-8
U6: SN74LVC1G14DCK; SOT-353
U7: AP7361C-3.3V; UDFN-8
U8: SN74LVC1G17DCK; SOT-353
U10: MCP73833_MSOP; MSOP-10_3x3mm_P0.5mm
U11: AP2112K-3.3; SOT23-5
U12: STLQ015-3.3; SOT23-5
U14: SN74LVC1G175DCK; SOT-323

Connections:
3.3V: C23.1, R10.1, R43.1, TP1.1, U11.5 (VOUT); also elsewhere on the board
3.3V_P: C21.1, TP7.1, U7.1 (VOUT); also elsewhere on the board
CHG_LED: D6.C, R42.2, U10.3 (STAT1); also elsewhere on the board
EN: R9.2, U14.4 (Q)
ESP19/CHG_STAT2: R10.2, U10.4 (STAT2); also elsewhere on the board
ESP27/PeripheralPower: U7.5 (EN); also elsewhere on the board
ESP32/PowerControl: Q5.3 (D); also elsewhere on the board
ESP33/FastOff: R35.2, R39.1; also elsewhere on the board
ESP34/CHG_STAT1: D6.A, R43.2; also elsewhere on the board
GND: C6.2, C7.2, C16.2, C17.2, C18.2, C19.2, C21.2, C22.2, C23.2, C24.2, C25.2, J2.1 (-), Q2.5 (S), Q4.2 (S), Q5.2 (S), R29.2, R30.1, R32.2, R39.2, TP4.1, TP23.1, U4.1 (CTG), U4.4 (GND), U4.6 (QSTRT), U4.9 (GND), U6.3 (GND), U7.4 (GND), U7.9 (EP), U8.3 (GND), U10.5 (VSS), U11.2 (GND), U12.2 (GND), U14.2 (GND); also elsewhere on the board
M_BACKUP: C25.1, TP9.1, U12.5 (VOUT); also elsewhere on the board
unnamed: C19.1, D5.C, R33.1, R34.1, U8.2
unnamed: Q2.3 (G), Q2.6 (D), R18.1
unnamed: Q2.1 (G), R9.1
unnamed: Q4.3 (D), R34.2
unnamed: Q4.1 (G), R35.1
unnamed: Q5.1 (G), R36.2
unnamed: R29.1, R30.2, R31.2
unnamed: R32.1, U10.6 (PROG)
unnamed: R31.1, U10.8 (THERM)
unnamed: R36.1, U6.4, U14.1 (CLK)
unnamed: U8.4, U14.6 (~CLR)
POWER_BTN: C18.1, D5.A, R22.2, R33.2, TP12.1, U6.2; also elsewhere on the board
VBATT: C6.1, C16.1, C24.1, D4.A, J2.2 (+), TP10.1, U4.2 (CELL), U4.3 (VDD), U10.9 (V_{BAT}), U10.10 (V_{BAT}), U12.1 (VIN), U12.3 (EN)
VIN: D3.C, D4.C, Q2.2 (1), R18.2, R22.1, TP11.1, U6.5 (VCC), U8.5 (VCC), U14.3 (D), U14.5 (VCC)
VRAW: C7.1, C22.1, Q2.4 (D), TP8.1, U7.8 (VIN), U11.1 (VIN), U11.3 (EN); also elsewhere on the board
VUSB: C17.1, D3.A, R42.1, U10.1 (VDD), U10.2 (VDD); also elsewhere on the board

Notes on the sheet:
High Side Switch
Charge current: 1000mA (1000V/Rprog)
Power Button on Membrane Overlay
Based on:
GNSS RTC Backup
Temp Cutoff: 0C to 42C
10k, +/-5%, B-Constant 3380
NCP18XH103J03RB
Soft Power Switch
LiPo Charger
Charger Status
Power Mux
Fuel Gauge
https://www.ti.com/lit/pdf/scea048
Peripheral 3.3V
Main 3.3V
7-bit unshifted I²C address: 0x36

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

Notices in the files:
parts and their libraries:
Released under the Creative Commons Attribution Share-Alike 4.0 License
https://creativecommons.org/licenses/by-sa/4.0
